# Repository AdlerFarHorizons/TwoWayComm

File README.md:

TwoWayComm
==========

Two-way wireless communication for telemetry and control.

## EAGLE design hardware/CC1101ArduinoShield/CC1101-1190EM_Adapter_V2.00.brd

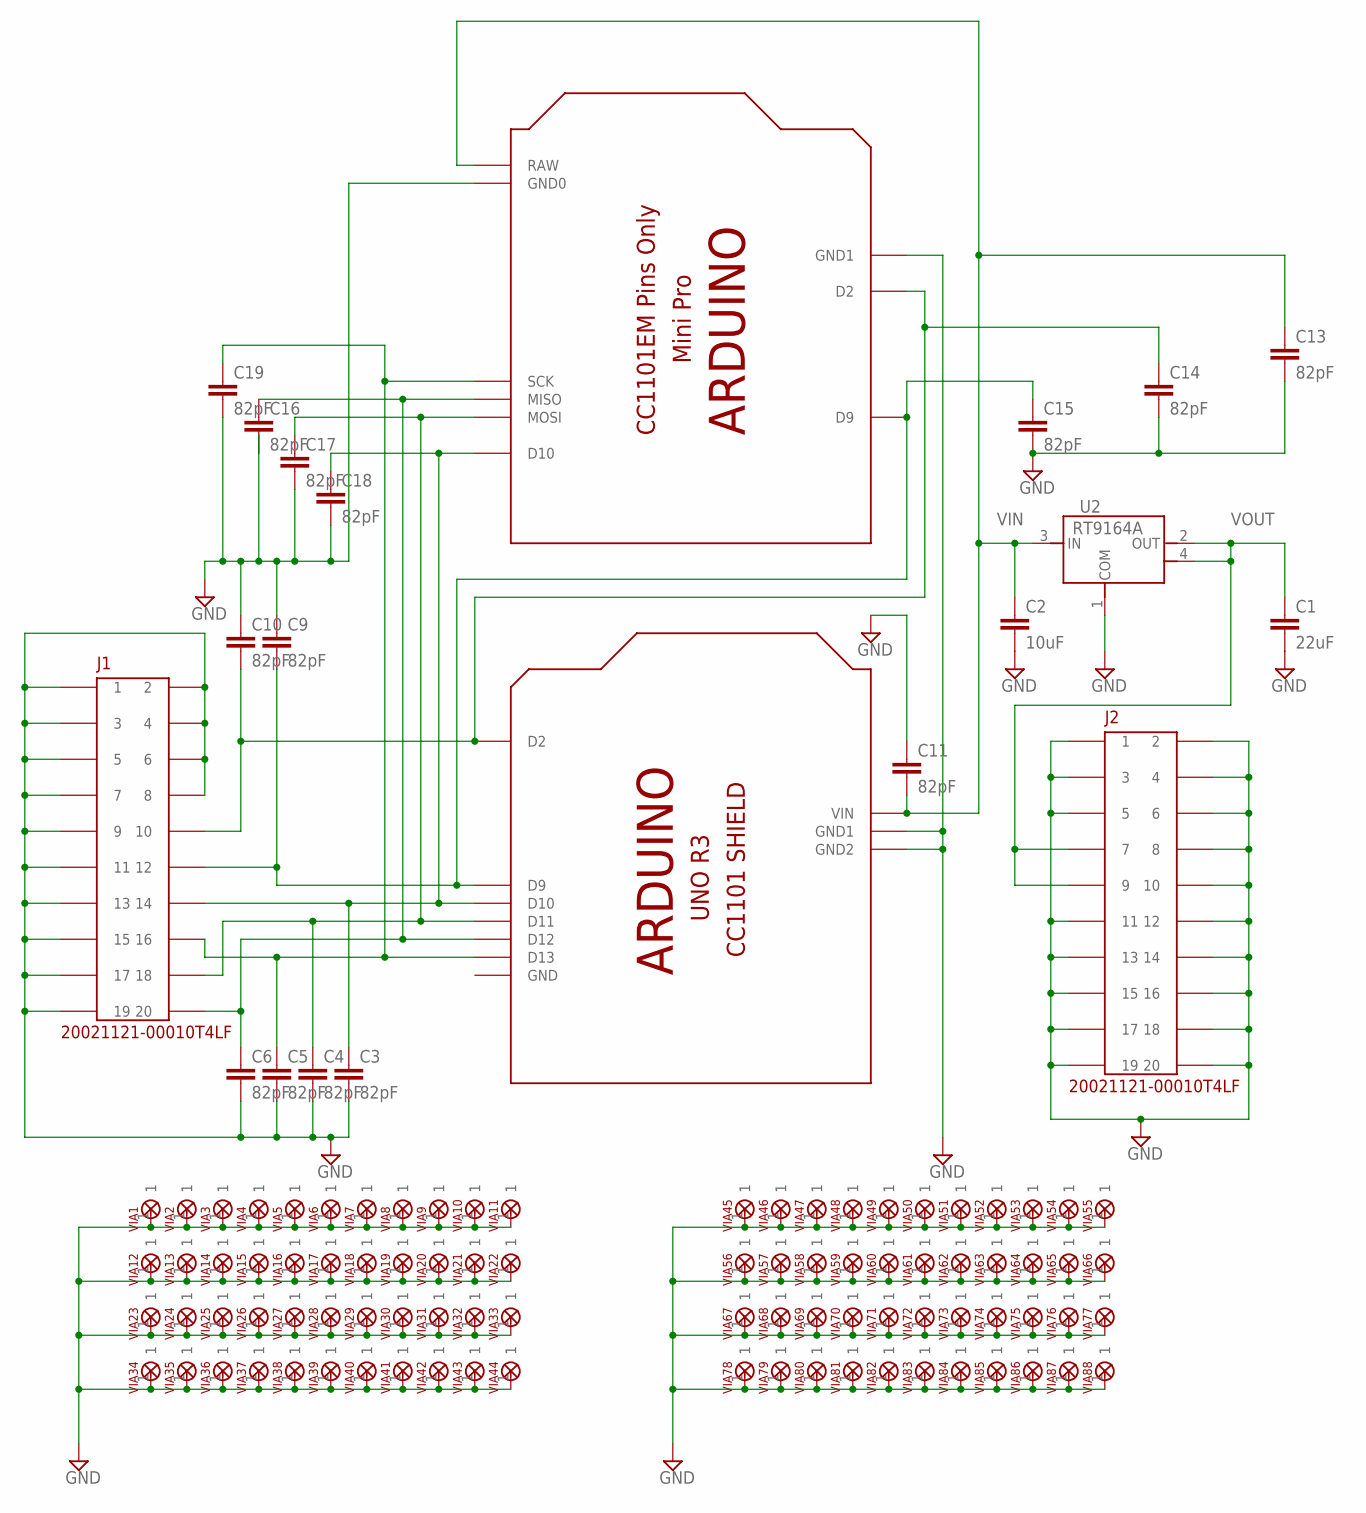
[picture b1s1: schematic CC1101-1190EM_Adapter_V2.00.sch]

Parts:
C1: 22uF; C1206
C2: 10uF; C1206
C3, C4, C5, C6, C9, C10, C11, C13, C14, C15, C16, C17, C18, C19: 82pF; C0805
J1, J2: 20021121-00010T4LF; PINHDR10X2_50X50MIL_SMT
U1: SHIELD-UNOR3-CC1101
U2: RT9164A; TO223
U$1: ARDUINOMINI_CC1101; ARDUINOMINI_CC1101_PINS_ONLY
VIA1, VIA2, VIA3, VIA4, VIA5, VIA6, VIA7, VIA8, VIA9, VIA10, VIA11, VIA12, VIA13, VIA14, VIA15, VIA16, VIA17, VIA18, VIA19, VIA20, VIA21, VIA22, VIA23, VIA24, VIA25, VIA26, VIA27, VIA28, VIA29, VIA30, VIA31, VIA32, VIA33, VIA34, VIA35, VIA36, VIA37, VIA38, VIA39, VIA40, VIA41, VIA42, VIA43, VIA44, VIA45, VIA46, VIA47, VIA48, VIA49, VIA50, VIA51, VIA52, VIA53, VIA54, VIA55, VIA56, VIA57, VIA58, VIA59, VIA60, VIA61, VIA62, VIA63, VIA64, VIA65, VIA66, VIA67, VIA68, VIA69, VIA70, VIA71, VIA72, VIA73, VIA74, VIA75, VIA76, VIA77, VIA78, VIA79, VIA80, VIA81, VIA82, VIA83, VIA84, VIA85, VIA86, VIA87, VIA88: GND_VIA_NO_THERMAL; VIA_NO_THERMAL

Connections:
GND: C1.2, C2.2, C3.2, C4.2, C5.2, C6.2, C9.1, C10.1, C11.1, C13.2, C14.2, C15.2, C17.2, C18.2, C19.2, J1.P$1 (1), J1.P$2 (2), J1.P$3 (3), J1.P$4 (4), J1.P$5 (5), J1.P$6 (6), J1.P$7 (7), J1.P$8 (8), J1.P$9 (9), J1.P$11 (11), J1.P$13 (13), J1.P$15 (15), J1.P$17 (17), J1.P$19 (19), J2.P$1 (1), J2.P$2 (2), J2.P$3 (3), J2.P$4 (4), J2.P$5 (5), J2.P$6 (6), J2.P$8 (8), J2.P$10 (10), J2.P$11 (11), J2.P$12 (12), J2.P$13 (13), J2.P$14 (14), J2.P$15 (15), J2.P$16 (16), J2.P$17 (17), J2.P$18 (18), J2.P$19 (19), J2.P$20 (20), U1.GND, U1.GND1, U1.GND2, U2.1 (COM), U$1.P$9 (GND1), U$1.P$20 (GND0), VIA1.1, VIA2.1, VIA3.1, VIA4.1, VIA5.1, VIA6.1, VIA7.1, VIA8.1, VIA9.1, VIA10.1, VIA11.1, VIA12.1, VIA13.1, VIA14.1, VIA15.1, VIA16.1, VIA17.1, VIA18.1, VIA19.1, VIA20.1, VIA21.1, VIA22.1, VIA23.1, VIA24.1, VIA25.1, VIA26.1, VIA27.1, VIA28.1, VIA29.1, VIA30.1, VIA31.1, VIA32.1, VIA33.1, VIA34.1, VIA35.1, VIA36.1, VIA37.1, VIA38.1, VIA39.1, VIA40.1, VIA41.1, VIA42.1, VIA43.1, VIA44.1, VIA45.1, VIA46.1, VIA47.1, VIA48.1, VIA49.1, VIA50.1, VIA51.1, VIA52.1, VIA53.1, VIA54.1, VIA55.1, VIA56.1, VIA57.1, VIA58.1, VIA59.1, VIA60.1, VIA61.1, VIA62.1, VIA63.1, VIA64.1, VIA65.1, VIA66.1, VIA67.1, VIA68.1, VIA69.1, VIA70.1, VIA71.1, VIA72.1, VIA73.1, VIA74.1, VIA75.1, VIA76.1, VIA77.1, VIA78.1, VIA79.1, VIA80.1, VIA81.1, VIA82.1, VIA83.1, VIA84.1, VIA85.1, VIA86.1, VIA87.1, VIA88.1
unnamed: C3.1, C18.1, J1.P$14 (14), U1.D10, U$1.P$30 (D10)
unnamed: C4.1, C17.1, J1.P$18 (18), U1.D11, U$1.P$29 (MOSI)
unnamed: C6.1, C16.1, J1.P$20 (20), U1.D12, U$1.P$28 (MISO)
unnamed: C5.1, C19.1, J1.P$16 (16), U1.D13, U$1.P$27 (SCK)
unnamed: C10.2, C14.1, J1.P$10 (10), U1.D2, U$1.P$7 (D2)
unnamed: C9.2, C15.1, J1.P$12 (12), U1.D9, U$1.P$1 (D9)
VIN: C2.1, C11.2, C13.1, U1.VIN, U2.3 (IN), U$1.P$19 (RAW)
VOUT: C1.1, J2.P$7 (7), J2.P$9 (9), U2.2 (OUT), U2.4 (OUT)

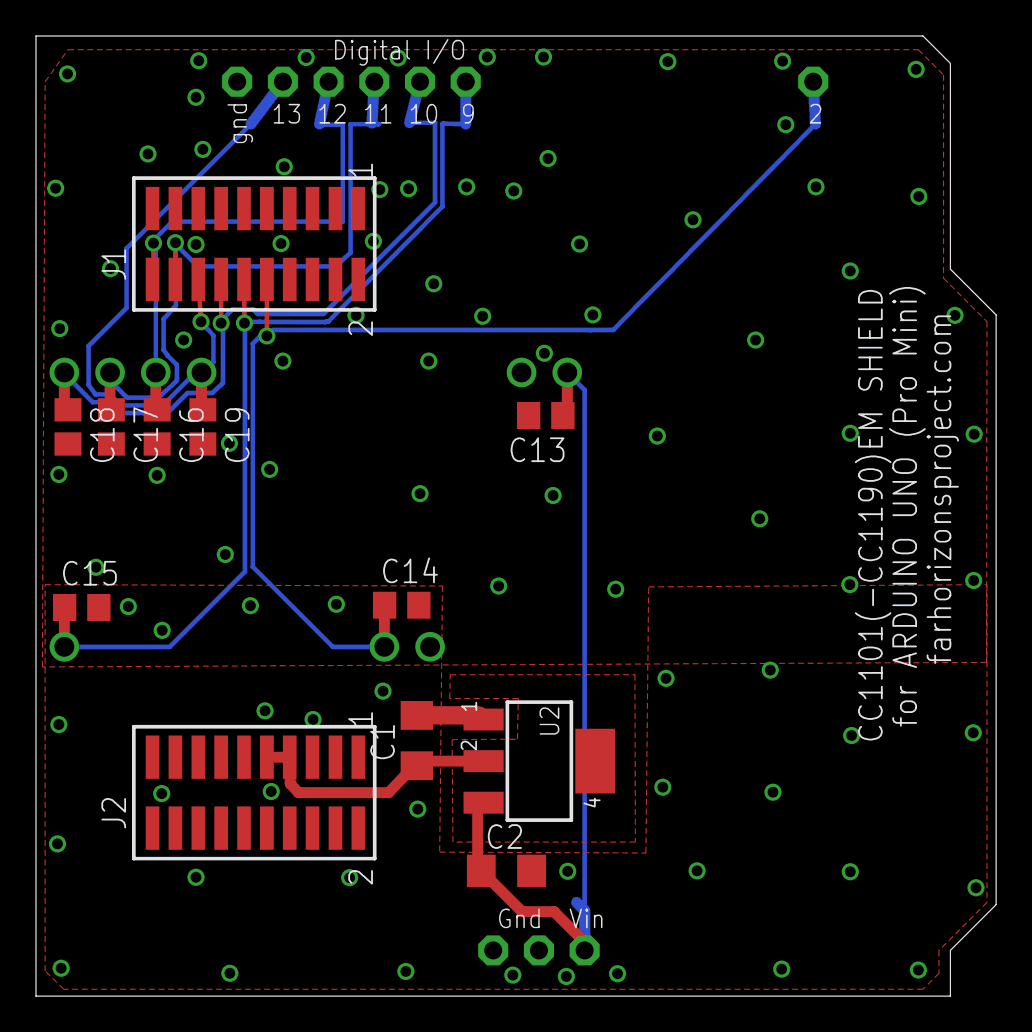
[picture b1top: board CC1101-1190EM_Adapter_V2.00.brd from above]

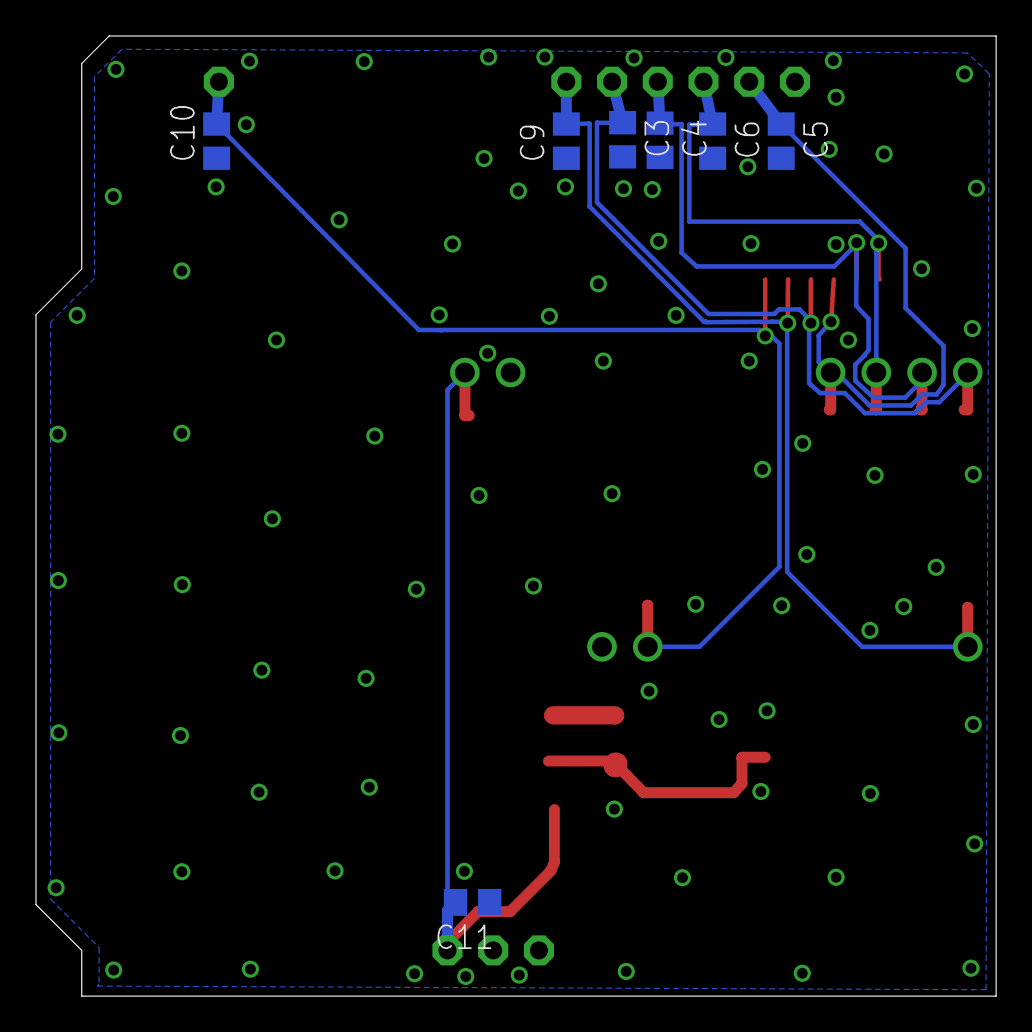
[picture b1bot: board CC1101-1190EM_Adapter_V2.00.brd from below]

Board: 2 copper layers, 53.3 x 53.3 mm, 109 parts (8 on the bottom side), 9 nets.

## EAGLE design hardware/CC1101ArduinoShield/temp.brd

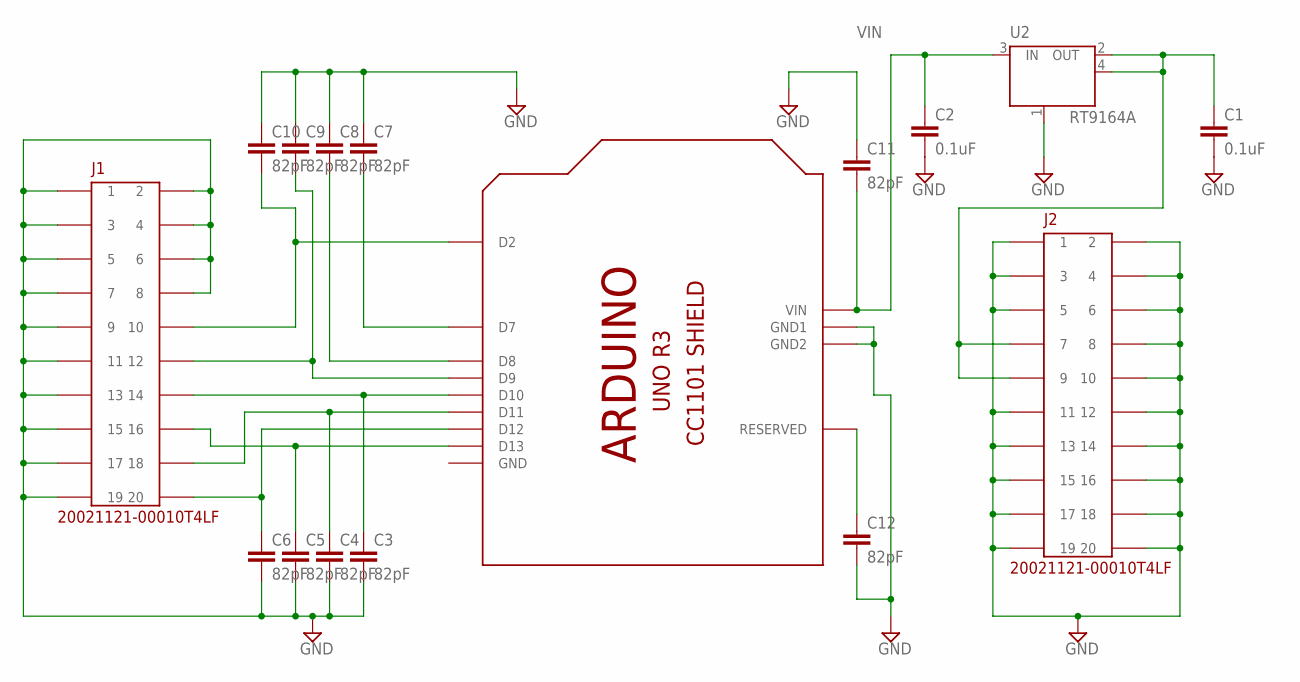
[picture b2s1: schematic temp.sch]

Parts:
C1, C2: 0.1uF; C1206
C3, C4, C5, C6, C7, C8, C9, C10, C11, C12: 82pF; C0805
J1, J2: 20021121-00010T4LF; PINHDR10X2_50X50MIL_SMT
U1: SHIELD-UNOR3-CC1101
U2: RT9164A; TO223

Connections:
GND: C1.2, C2.2, C3.2, C4.2, C5.2, C6.2, C7.1, C8.1, C9.1, C10.1, C11.1, C12.2, J1.P$1 (1), J1.P$2 (2), J1.P$3 (3), J1.P$4 (4), J1.P$5 (5), J1.P$6 (6), J1.P$7 (7), J1.P$8 (8), J1.P$9 (9), J1.P$11 (11), J1.P$13 (13), J1.P$15 (15), J1.P$17 (17), J1.P$19 (19), J2.P$1 (1), J2.P$2 (2), J2.P$3 (3), J2.P$4 (4), J2.P$5 (5), J2.P$6 (6), J2.P$8 (8), J2.P$10 (10), J2.P$11 (11), J2.P$12 (12), J2.P$13 (13), J2.P$14 (14), J2.P$15 (15), J2.P$16 (16), J2.P$17 (17), J2.P$18 (18), J2.P$19 (19), J2.P$20 (20), U1.GND, U1.GND1, U1.GND2, U2.1 (GND/ADJ)
unnamed: C3.1, J1.P$14 (14), U1.D10
unnamed: C4.1, J1.P$18 (18), U1.D11
unnamed: C6.1, J1.P$20 (20), U1.D12
unnamed: C5.1, J1.P$16 (16), U1.D13
unnamed: C10.2, J1.P$10 (10), U1.D2
unnamed: C9.2, J1.P$12 (12), U1.D9
unnamed: C1.1, J2.P$7 (7), J2.P$9 (9), U2.2 (OUT), U2.4 (OUT)
unnamed: C8.2, U1.D8
unnamed: C7.2, U1.D7
unnamed: C12.1, U1.RESERVED
VIN: C2.1, C11.2, U1.VIN, U2.3 (IN)

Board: 2 copper layers, 16 parts (0 on the bottom side), 12 nets, no tracks yet.

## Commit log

2013-06-25 First real commit.
2013-08-22 New stuff
2014-01-31 General update
